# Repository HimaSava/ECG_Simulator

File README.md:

# ECG_Simulator

This project was part of my Winter Internship 2018 at Streben Healthcare Pvt. Ltd.

### Objective
To create an bluetooth enabled ECG simulator that can mimic the existing system and can trasfer the data without the need for an human subject to be connected to it.

The system should be compact and can replace the existing ECG simulators that are bulky and a hassel to carry around as well as to connect with the software physically.

### A bit about the system:
This ECG simulator was made to mimic the ECG data input from an standard ECG machine. And so the communication protocol is being followed as per the standard. 

Other than that this project is a basic Bluetooth enabled Arduino shield project. The multiple ECG datas are stored on the Arduino and the user can choose between them from the on the board switchs. 

The whole system is conpact and can be easily use a standard mobile powerbank as a power source making it very trasportable.

#### This project was coded and executed by using the following softwares:
* CodeBlocks (C++)
* Arduino IDE (C++)
* Termite (Serial Debugging)
* Eagle 7.6.0 (PCB Designing)

### Contents of the Repository
1. A complete PCB Design with the gerber files aready created.
2. A small C++ application to run on the computer for debugging the data transfer from the Device using bluetooth or USB.
3. The final Arduino code with the preprogrammed ECG Data.
4. Few images of the schematic and final board and PCB Designs.
5. A final Internship Report for the Project.

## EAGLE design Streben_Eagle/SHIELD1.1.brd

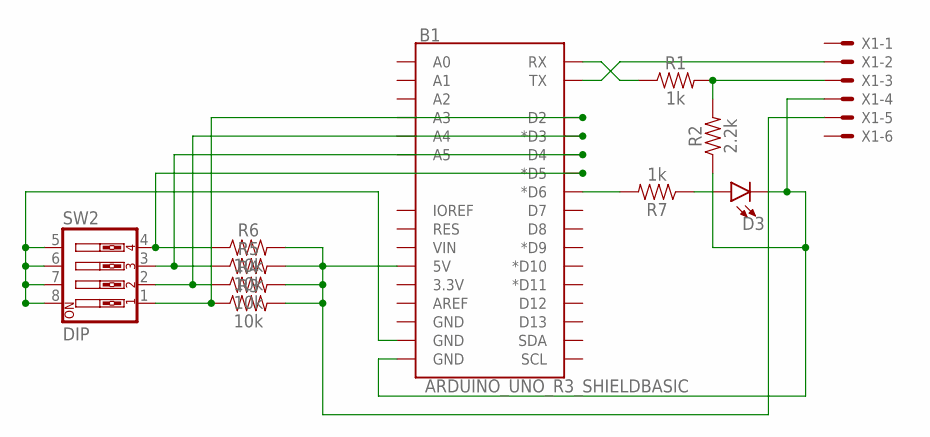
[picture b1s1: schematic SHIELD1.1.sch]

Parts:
B1: ARDUINO_UNO_R3_SHIELDBASIC; UNO_R3_SHIELD
D3: LED5MM; LED_5MM
R1, R7: 1k; AXIAL-0.3
R2: 2.2k; AXIAL-0.3
R3, R4, R5, R6: 10k; AXIAL-0.3
SW2: DIP; EDG-04
X1: 22-23-2061

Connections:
5V: B1.GND@1 (GND), SW2.5, SW2.6, SW2.7, SW2.8
D2: B1.D2, R3.P$1 (1), SW2.1
D3: B1.D3 (*D3), R4.P$1 (1), SW2.2
GND: B1.GND@0 (GND), D3.K (C), R2.P$1 (1), X1.4
LED: D3.A, R7.P$1 (1)
unnamed: B1.D5 (*D5), R6.P$1 (1), SW2.4
unnamed: B1.RX, R1.P$1 (1)
unnamed: B1.D4, R5.P$1 (1), SW2.3
unnamed: B1.TX, X1.2
unnamed: R1.P$2 (2), R2.P$2 (2), X1.3
unnamed: B1.5V, R3.P$2 (2), R4.P$2 (2), R5.P$2 (2), R6.P$2 (2), X1.5
unnamed: B1.D6 (*D6), R7.P$2 (2)

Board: 2 copper layers, 11 parts (0 on the bottom side), 12 nets, no tracks yet.

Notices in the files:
parts and their libraries:
SparkFun-Boards: Licensing: Creative Commons ShareAlike 4.0 International - https://creativecommons.org/licenses/by-sa/4.0
